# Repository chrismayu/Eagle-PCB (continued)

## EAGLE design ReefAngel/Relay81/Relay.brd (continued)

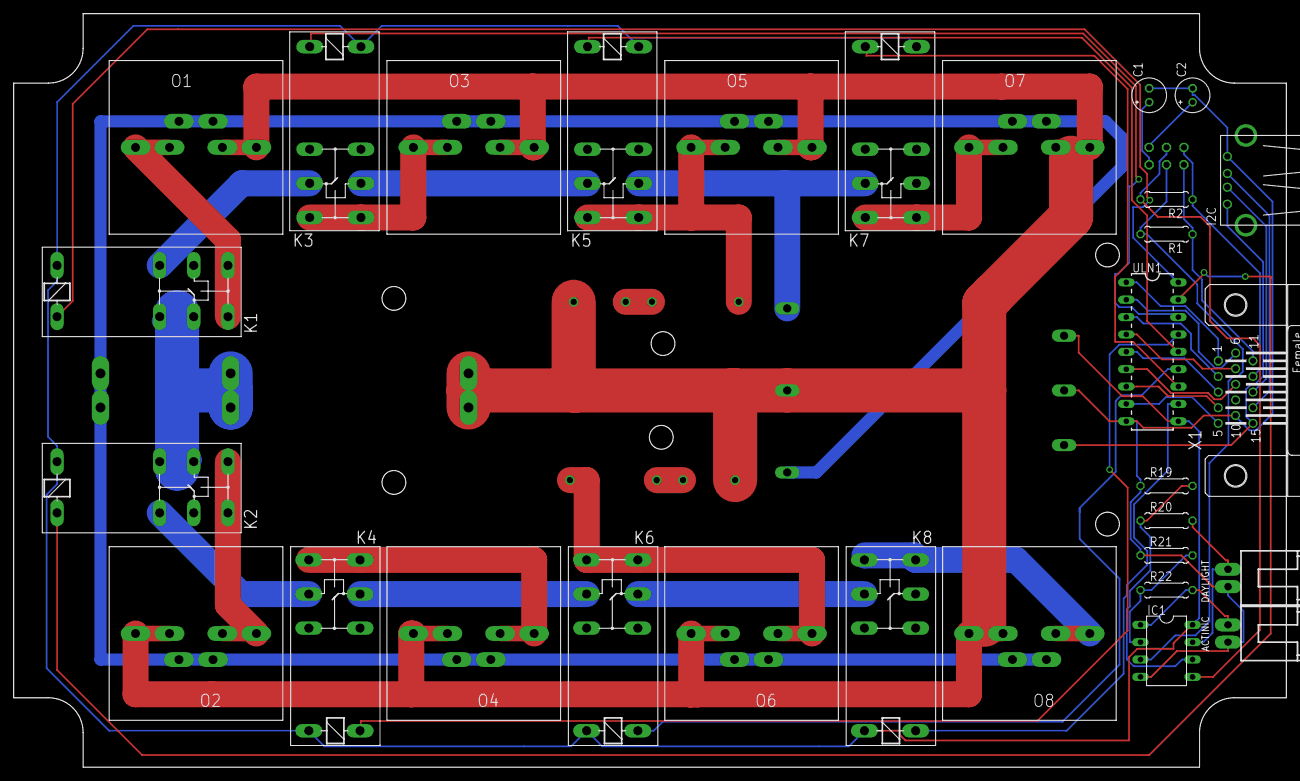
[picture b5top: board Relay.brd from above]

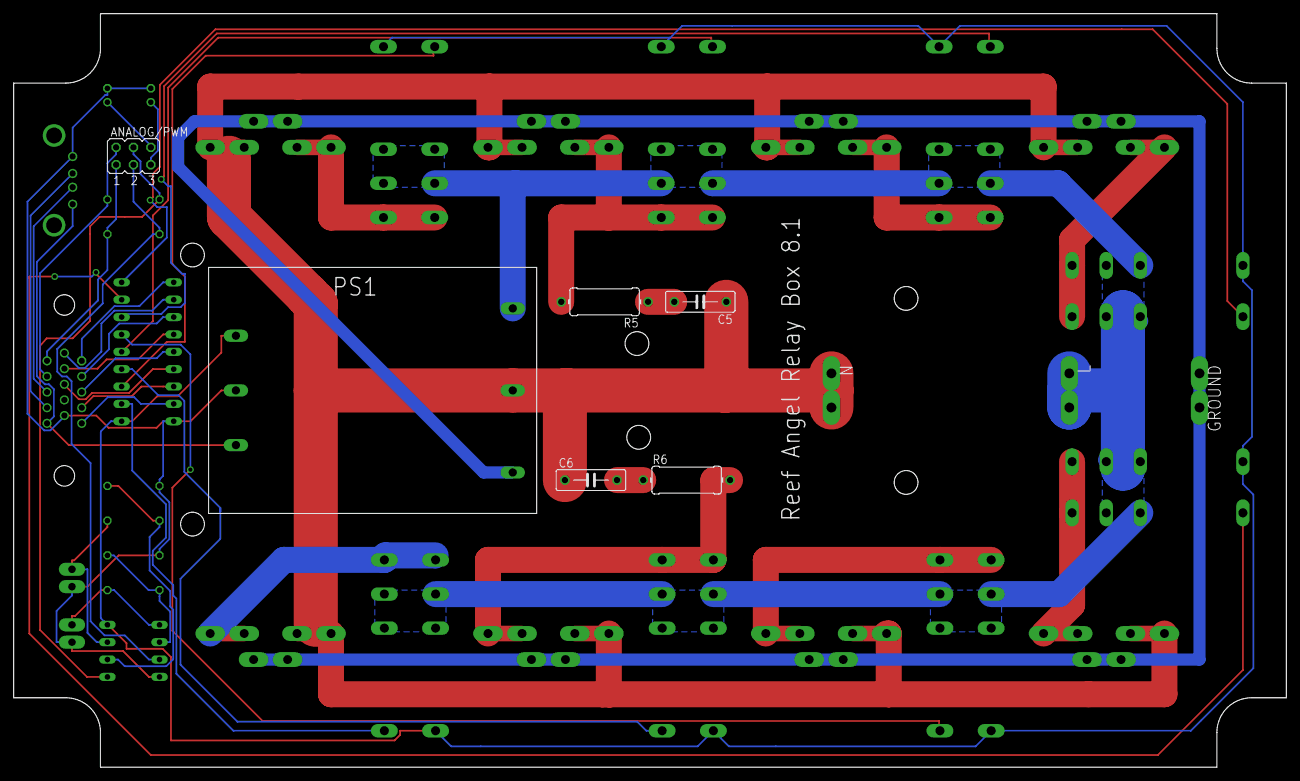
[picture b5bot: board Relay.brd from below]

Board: 2 copper layers, 186.2 x 110.2 mm, 39 parts (9 on the bottom side), 44 nets.

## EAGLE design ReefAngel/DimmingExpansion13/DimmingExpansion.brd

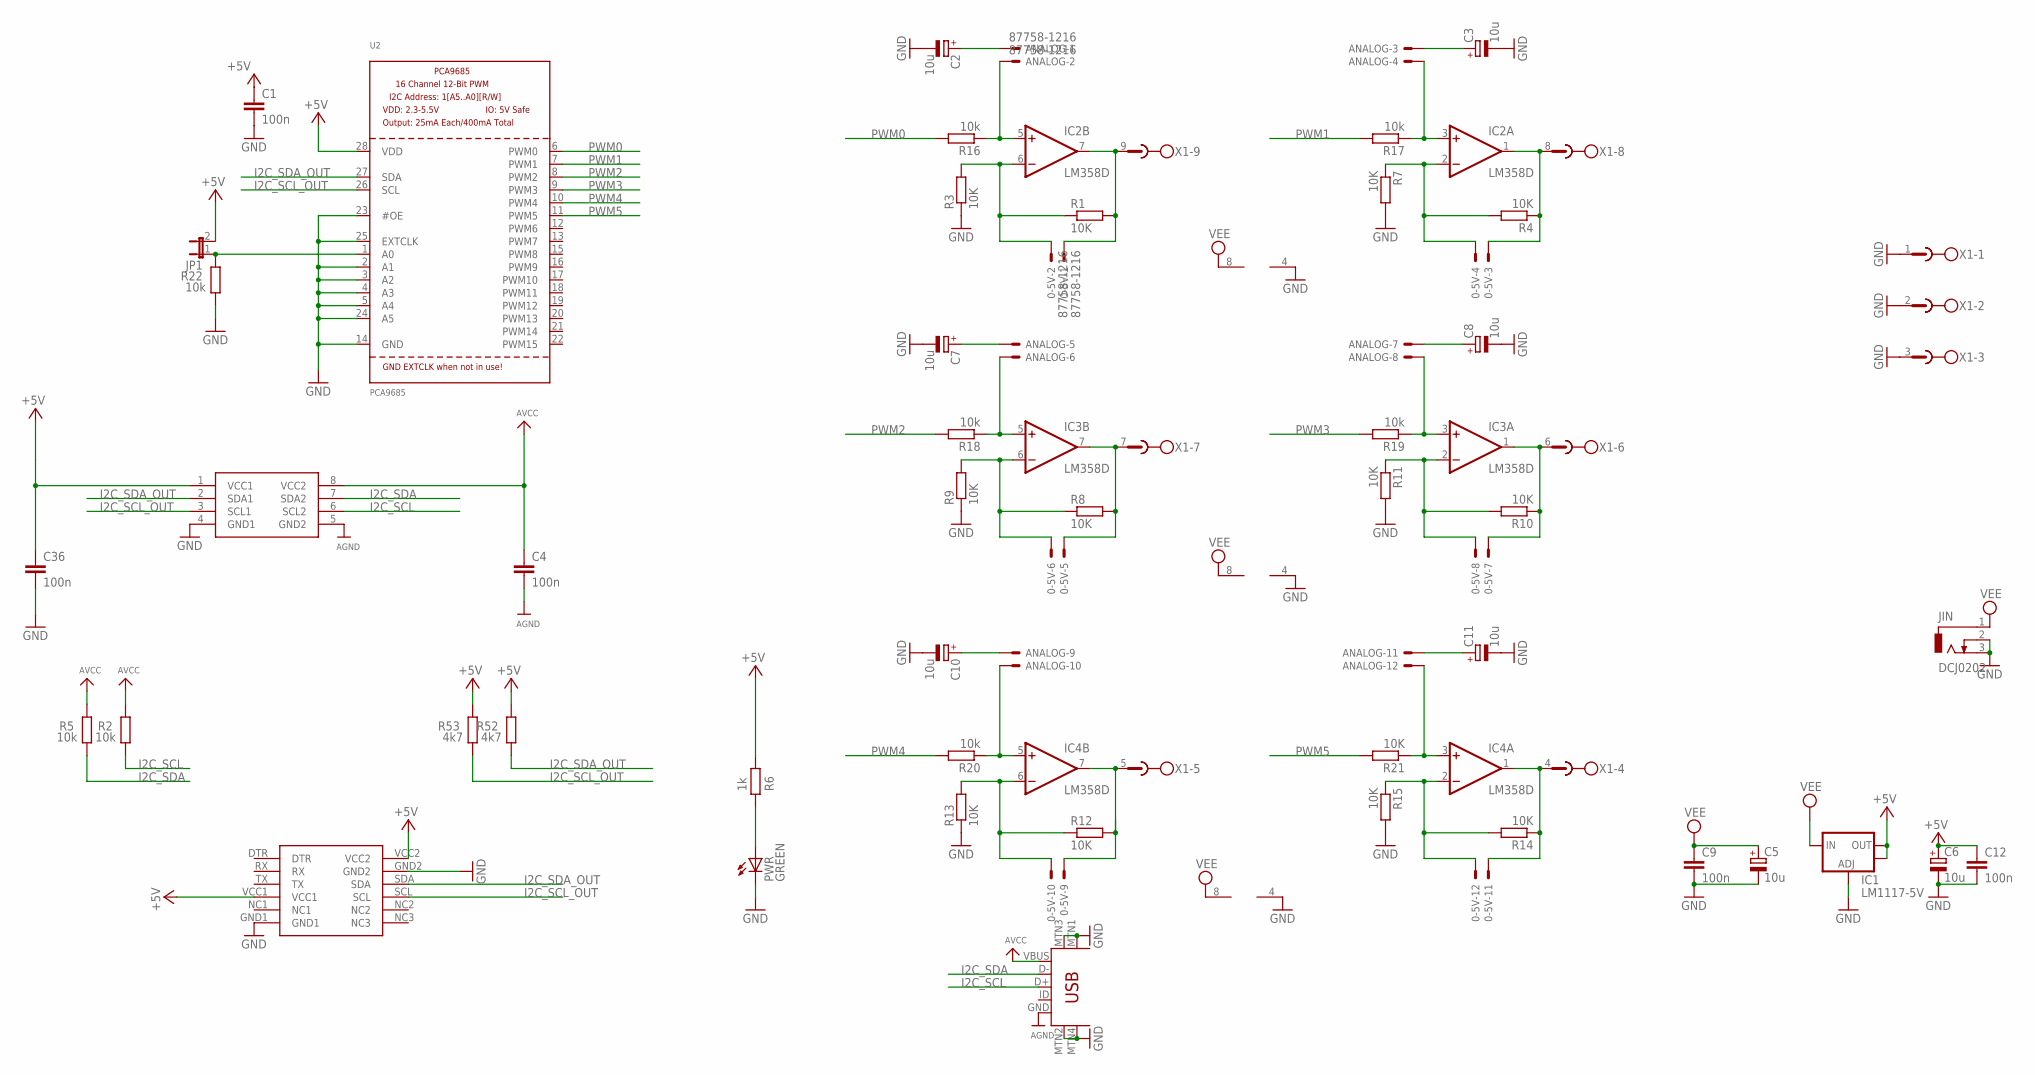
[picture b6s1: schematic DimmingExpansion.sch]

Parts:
0-5V: 87758-1216
ANALOG: 87758-1216
C1, C4, C9, C12, C36: 100n; C0805
C2, C3, C5, C6, C7, C8, C10, C11: 10u; A/3216-18W
IC1: LM1117-5V; SOT223
IC2, IC3, IC4: LM358D; SO08
JIN: DCJ0202
JP1: JP1E; JP1
PWR: GREEN; LED3MM
R1, R3, R4, R7, R8, R9, R10, R11, R12, R13, R14, R15, R21: 10K; R0805
R2, R5, R16, R17, R18, R19, R20, R22: 10k; R0805
R6: 1k; R0805
R52, R53: 4k7; R0805
U1: ADUM1250; SO08
U2: PCA9685; TSSOP28
U$2: RANET_RECEIVERRANET; RANET_RECEIVER
U$11: USB-MINIB-5PIN; USB-MINIB
X1: MSTBV9

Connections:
+5V: C1.1, C6.+, C12.1, C36.1, IC1.2 (OUT), IC1.4 (OUT), JP1.2, R6.1, R52.2, R53.2, U1.1 (VCC1), U2.28 (VDD), U$2.VCC1, U$2.VCC2
AGND: C4.2, U1.5 (GND2), U$11.GND
AVCC: C4.1, R2.2, R5.2, U1.8 (VCC2), U$11.VBUS
GND: C1.2, C2.-, C3.-, C5.-, C6.-, C7.-, C8.-, C9.2, C10.-, C11.-, C12.2, C36.2, IC1.1 (ADJ), IC2.4 (V-), IC3.4 (V-), IC4.4 (V-), JIN.2, JIN.3, PWR.K (C), R3.1, R7.2, R9.1, R11.2, R13.1, R15.2, R22.1, U1.4 (GND1), U2.2 (A1), U2.3 (A2), U2.4 (A3), U2.5 (A4), U2.14 (GND), U2.23 (#OE), U2.24 (A5), U2.25 (EXTCLK), U$2.GND1, U$2.GND2, U$11.MTN1 (MTN2), U$11.MTN2 (MTN3), U$11.MTN3 (MTN1), U$11.MTN4, X1.1, X1.2, X1.3
I2C_SCL: R2.1, U1.6 (SCL2), U$11.D+
I2C_SCL_OUT: R53.1, U1.3 (SCL1), U2.26 (SCL), U$2.SCL
I2C_SDA: R5.1, U1.7 (SDA2), U$11.D-
I2C_SDA_OUT: R52.1, U1.2 (SDA1), U2.27 (SDA), U$2.SDA
unnamed: ANALOG.2, IC2.5 (+IN), R16.1
unnamed: ANALOG.4, IC2.3 (+IN), R17.1
unnamed: 0-5V.5, IC3.7 (OUT), R8.2, X1.7
unnamed: 0-5V.1, IC2.7 (OUT), R1.2, X1.9
unnamed: ANALOG.1, C2.+
unnamed: 0-5V.3, IC2.1 (OUT), R4.1, X1.8
unnamed: ANALOG.3, C3.+
unnamed: 0-5V.6, IC3.6 (-IN), R8.1, R9.2
unnamed: 0-5V.9, IC4.7 (OUT), R12.2, X1.5
unnamed: PWR.A, R6.2
unnamed: 0-5V.7, IC3.1 (OUT), R10.1, X1.6
unnamed: ANALOG.6, IC3.5 (+IN), R18.1
unnamed: ANALOG.8, IC3.3 (+IN), R19.1
unnamed: 0-5V.8, IC3.2 (-IN), R10.2, R11.1
unnamed: ANALOG.10, IC4.5 (+IN), R20.1
unnamed: 0-5V.11, IC4.1 (OUT), R14.1, X1.4
unnamed: 0-5V.10, IC4.6 (-IN), R12.1, R13.2
unnamed: 0-5V.12, IC4.2 (-IN), R14.2, R15.1
unnamed: ANALOG.12, IC4.3 (+IN), R21.1
unnamed: ANALOG.5, C7.+
unnamed: ANALOG.7, C8.+
unnamed: ANALOG.9, C10.+
unnamed: ANALOG.11, C11.+
unnamed: JP1.1, R22.2, U2.1 (A0)
unnamed: 0-5V.2, IC2.6 (-IN), R1.1, R3.2
unnamed: 0-5V.4, IC2.2 (-IN), R4.2, R7.1
PWM0: R16.2, U2.6 (PWM0)
PWM1: R17.2, U2.7 (PWM1)
PWM2: R18.2, U2.8 (PWM2)
PWM3: R19.2, U2.9 (PWM3)
PWM4: R20.2, U2.10 (PWM4)
PWM5: R21.2, U2.11 (PWM5)
VEE: C5.+, C9.1, IC1.3 (IN), IC2.8 (V+), IC3.8 (V+), IC4.8 (V+), JIN.1

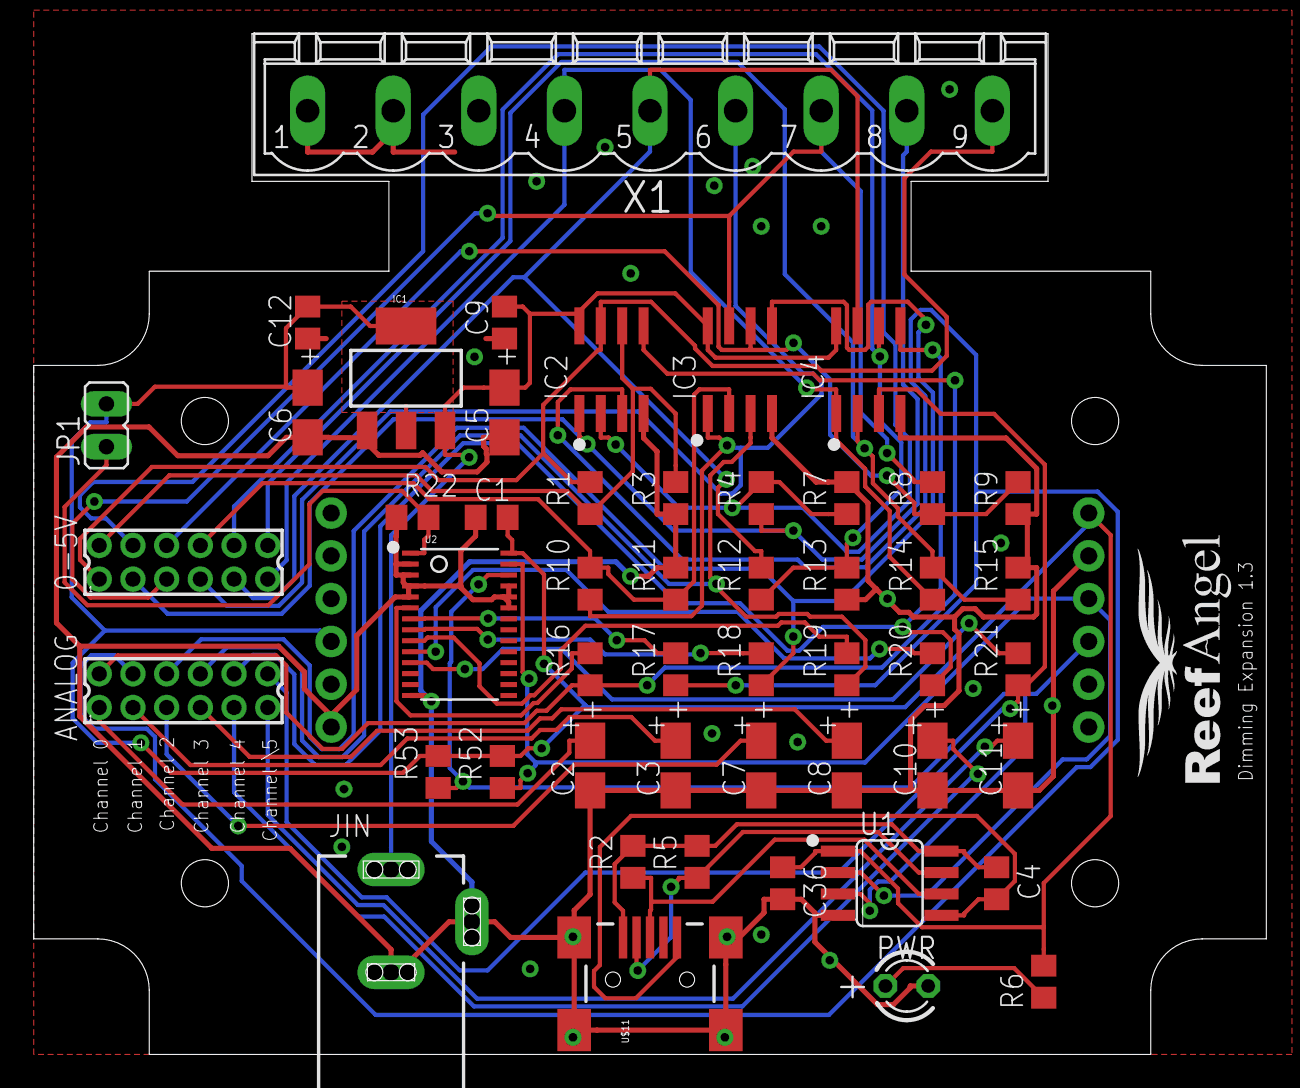
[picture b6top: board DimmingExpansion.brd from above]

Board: 2 copper layers, 73.2 x 60.6 mm, 51 parts (0 on the bottom side), 41 nets.

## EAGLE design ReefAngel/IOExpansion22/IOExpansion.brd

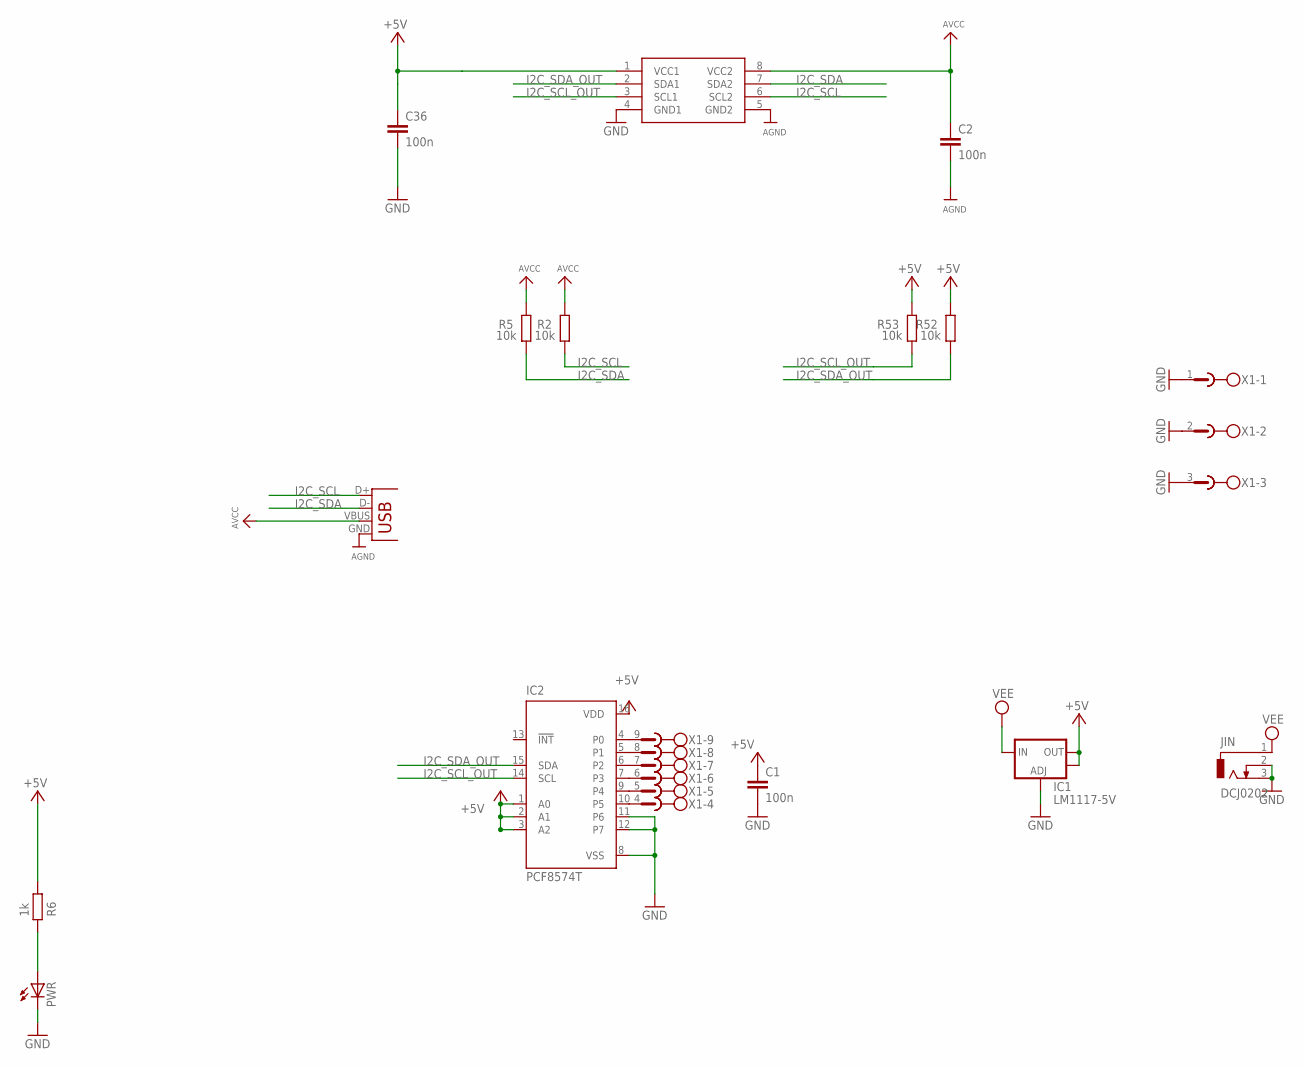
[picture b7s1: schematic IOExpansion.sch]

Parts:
C1, C2, C36: 100n; C0805
IC1: LM1117-5V; SOT223
IC2: PCF8574T; SO16W
JIN: DCJ0202
PWR: LED3MM
R2, R5, R52, R53: 10k; R0805
R6: 1k; R0805
U2: ADUM1250; SO08
X1: MSTBV9
X5: USBSMD; USB-MINIB

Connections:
+5V: C1.1, C36.1, IC1.2 (OUT), IC1.4 (OUT), IC2.1 (A0), IC2.2 (A1), IC2.3 (A2), IC2.16 (VDD), R6.1, R52.2, R53.2, U2.1 (VCC1)
AGND: C2.2, U2.5 (GND2), X5.GND
AVCC: C2.1, R2.2, R5.2, U2.8 (VCC2), X5.VBUS
GND: C1.2, C36.2, IC1.1 (ADJ), IC2.8 (VSS), IC2.11 (P6), IC2.12 (P7), JIN.2, JIN.3, PWR.K (C), U2.4 (GND1), X1.1, X1.2, X1.3
I2C_SCL: R2.1, U2.6 (SCL2), X5.D+
I2C_SCL_OUT: IC2.14 (SCL), R53.1, U2.3 (SCL1)
I2C_SDA: R5.1, U2.7 (SDA2), X5.D-
I2C_SDA_OUT: IC2.15 (SDA), R52.1, U2.2 (SDA1)
unnamed: IC2.10 (P5), X1.4
unnamed: IC2.9 (P4), X1.5
unnamed: IC2.7 (P3), X1.6
unnamed: IC2.6 (P2), X1.7
unnamed: IC2.5 (P1), X1.8
unnamed: IC2.4 (P0), X1.9
unnamed: PWR.A, R6.2
VEE: IC1.3 (IN), JIN.1

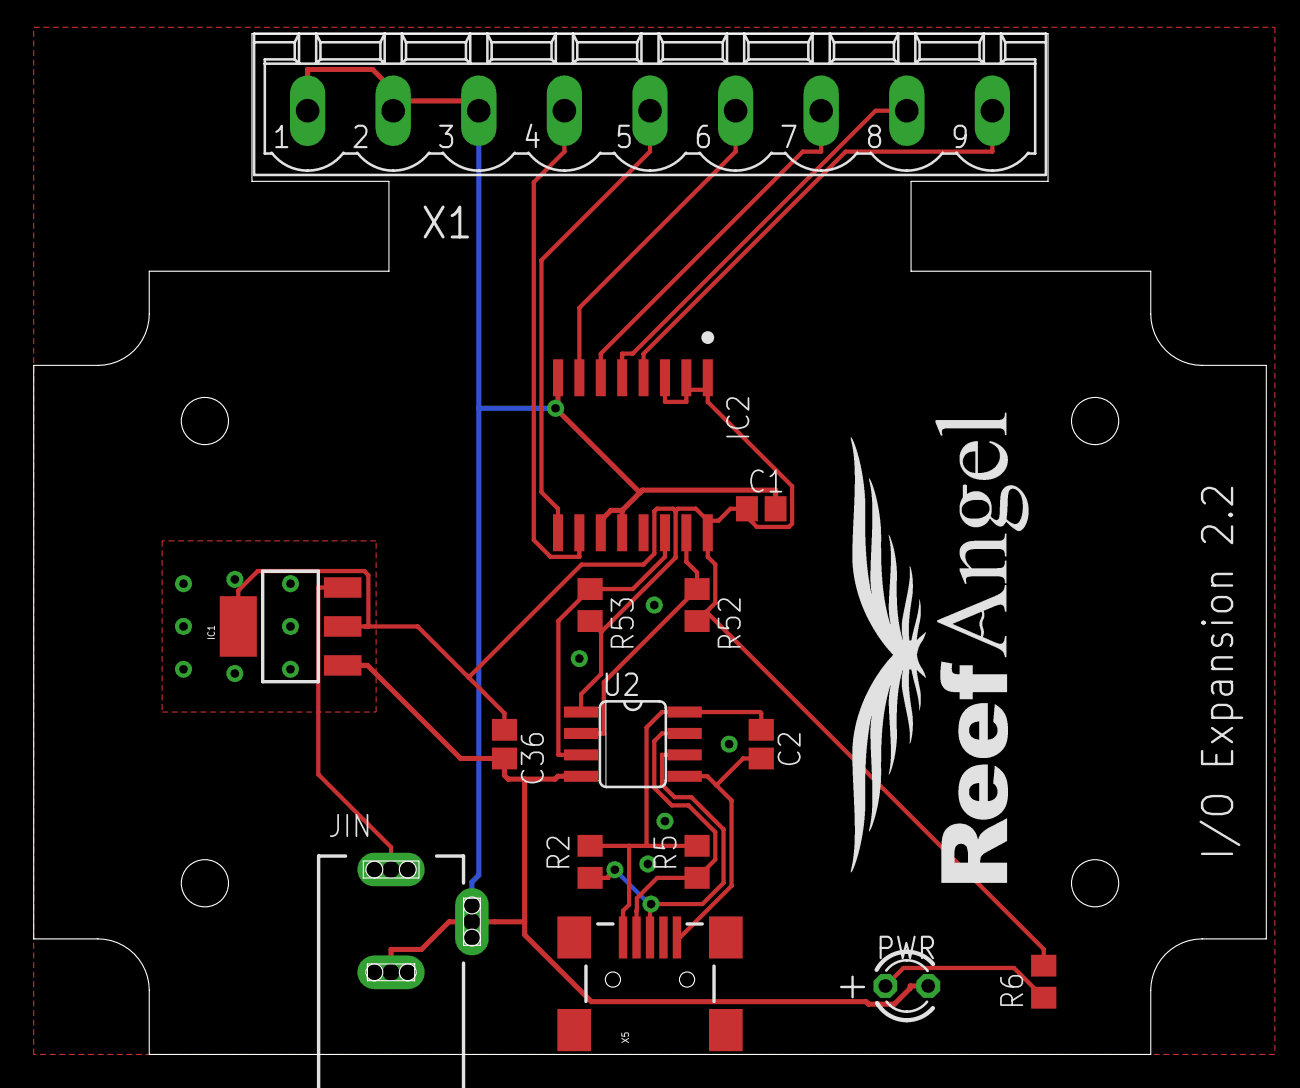
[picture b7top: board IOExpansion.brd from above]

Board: 2 copper layers, 73.2 x 60.6 mm, 15 parts (0 on the bottom side), 16 nets.

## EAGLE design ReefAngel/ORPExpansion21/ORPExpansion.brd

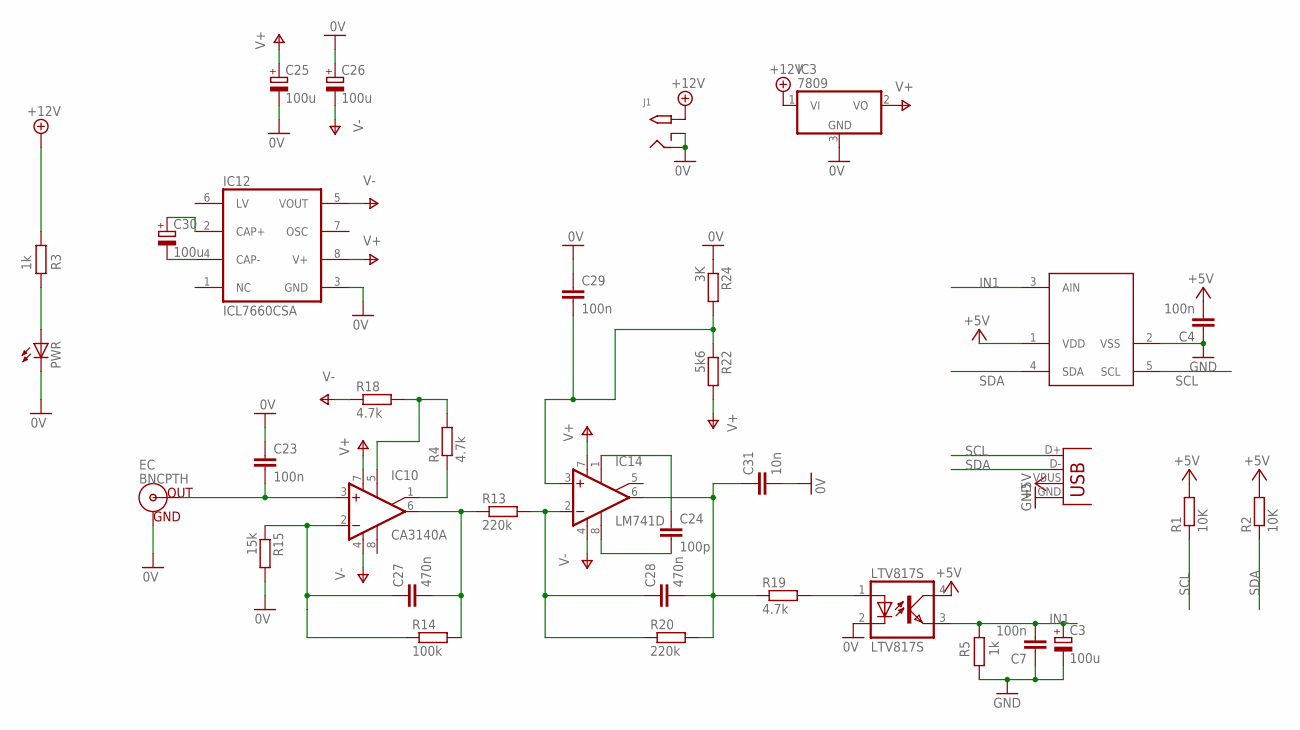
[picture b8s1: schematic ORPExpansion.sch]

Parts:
C3, C25, C26, C30: 100u; PANASONIC_D
C4, C7: 100n; C0805K
C23, C29: 100n; C0805
C24: 100p; C0805
C27, C28: 470n; C0805
C31: 10n; C0805
EC: BNCPTH; BNC
IC3: 7809; TO252
IC10: CA3140A; SO08
IC12: ICL7660CSA; SO08
IC14: LM741D; SO08
J1: 2.1MMJACKTHM; PJ-102A
LTV817S: LTV817S; SMD4
PWR: LED3MM
R1, R2: 10K; R0805
R3, R5: 1k; R0805
R4, R18, R19: 4.7k; R0805
R13, R20: 220k; R0805
R14: 100k; R0805
R15: 15k; R0805
R22: 5k6; R0805
R24: 3K; R0805
U$2: MCP3221; SOT23-5
X5: USBSMD; USB-MINIB

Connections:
0V: C23.1, C25.-, C26.+, C29.1, C31.2, EC.GND, IC3.3 (GND), IC12.3 (GND), J1.RING, J1.RING_SW, LTV817S.2 (C), PWR.K (C), R15.2, R24.1
+5V: C4.2, LTV817S.4 (COL), R1.2, R2.2, U$2.1 (VDD), X5.VBUS
+12V: IC3.1 (VI), J1.TIP, R3.1
GND: C3.-, C4.1, C7.1, R5.1, U$2.2 (VSS), X5.GND
IN1: C3.+, C7.2, LTV817S.3 (EMIT), R5.2, U$2.3 (AIN)
unnamed: PWR.A, R3.2
unnamed: C24.1, IC14.1 (ON1)
unnamed: C29.2, IC14.3 (+IN), R22.1, R24.2
unnamed: C30.-, IC12.4 (CAP-)
unnamed: C30.+, IC12.2 (CAP+)
unnamed: C23.2, EC.S (OUT), IC10.3 (+IN)
unnamed: C24.2, IC14.8 (OPT)
unnamed: C27.2, IC10.6 (OUT), R13.1, R14.2
unnamed: C27.1, IC10.2 (-IN), R14.1, R15.1
unnamed: IC10.5 (ON), R4.2, R18.2
unnamed: IC10.1 (ON/CMP), R4.1
unnamed: C28.1, IC14.2 (-IN), R13.2, R20.1
unnamed: LTV817S.1 (A), R19.2
unnamed: C28.2, C31.1, IC14.6 (OUT), R19.1, R20.2
SCL: R1.1, U$2.5 (SCL), X5.D+
SDA: R2.1, U$2.4 (SDA), X5.D-
V+: C25.+, IC3.2 (VO), IC10.7 (V+), IC12.8 (V+), IC14.7 (V+), R22.2
V-: C26.-, IC10.4 (V-), IC12.5 (VOUT), IC14.4 (V-), R18.1

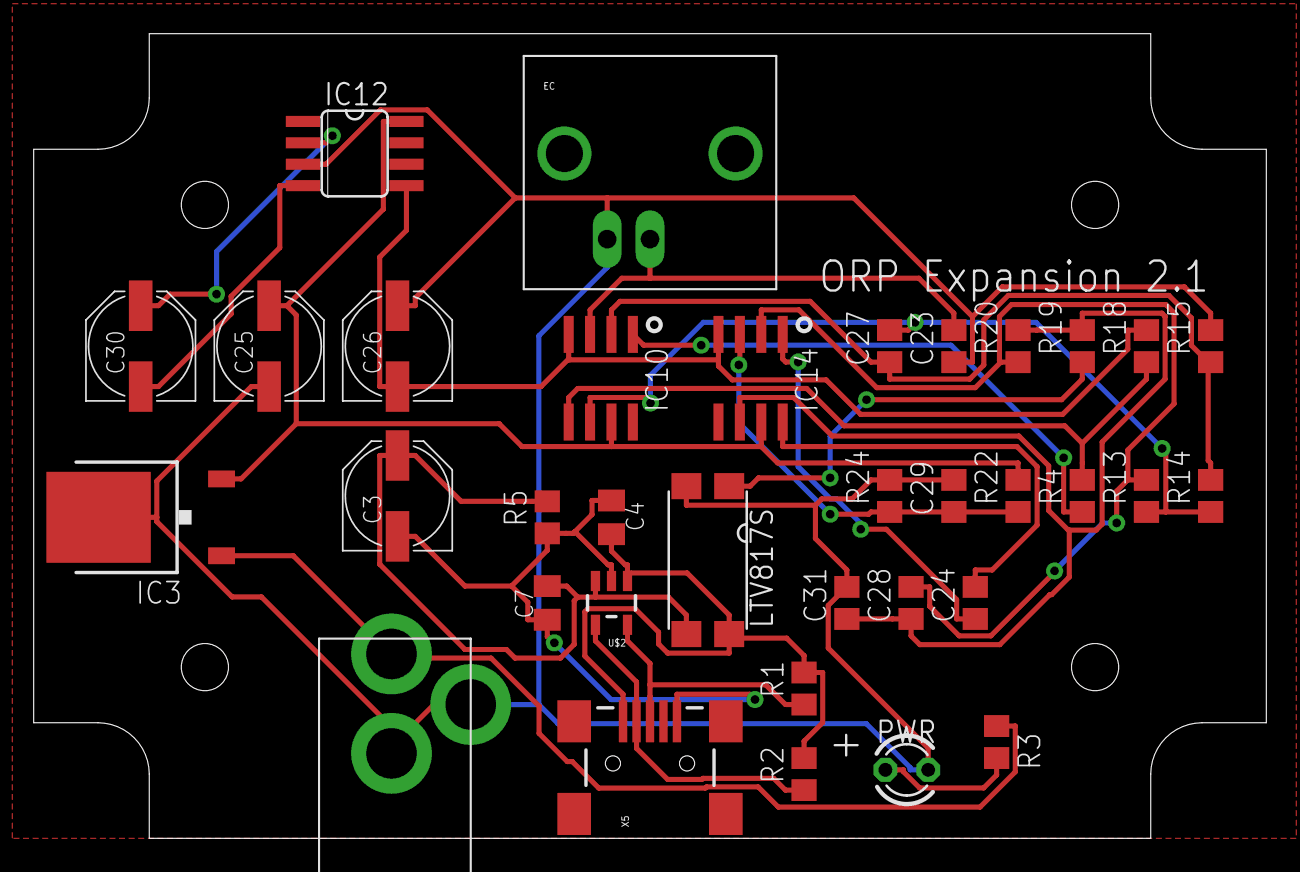
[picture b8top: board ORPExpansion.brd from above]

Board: 2 copper layers, 73.2 x 47.8 mm, 35 parts (0 on the bottom side), 23 nets.

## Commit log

2014-10-24 Init
2015-06-03 ds2482
2017-12-18 files update
2018-02-22 hive updates
2018-02-22 added reef angel
2018-02-22 added Smart Citizen
2018-03-06 sync
2018-03-09 atomsphere scanner
